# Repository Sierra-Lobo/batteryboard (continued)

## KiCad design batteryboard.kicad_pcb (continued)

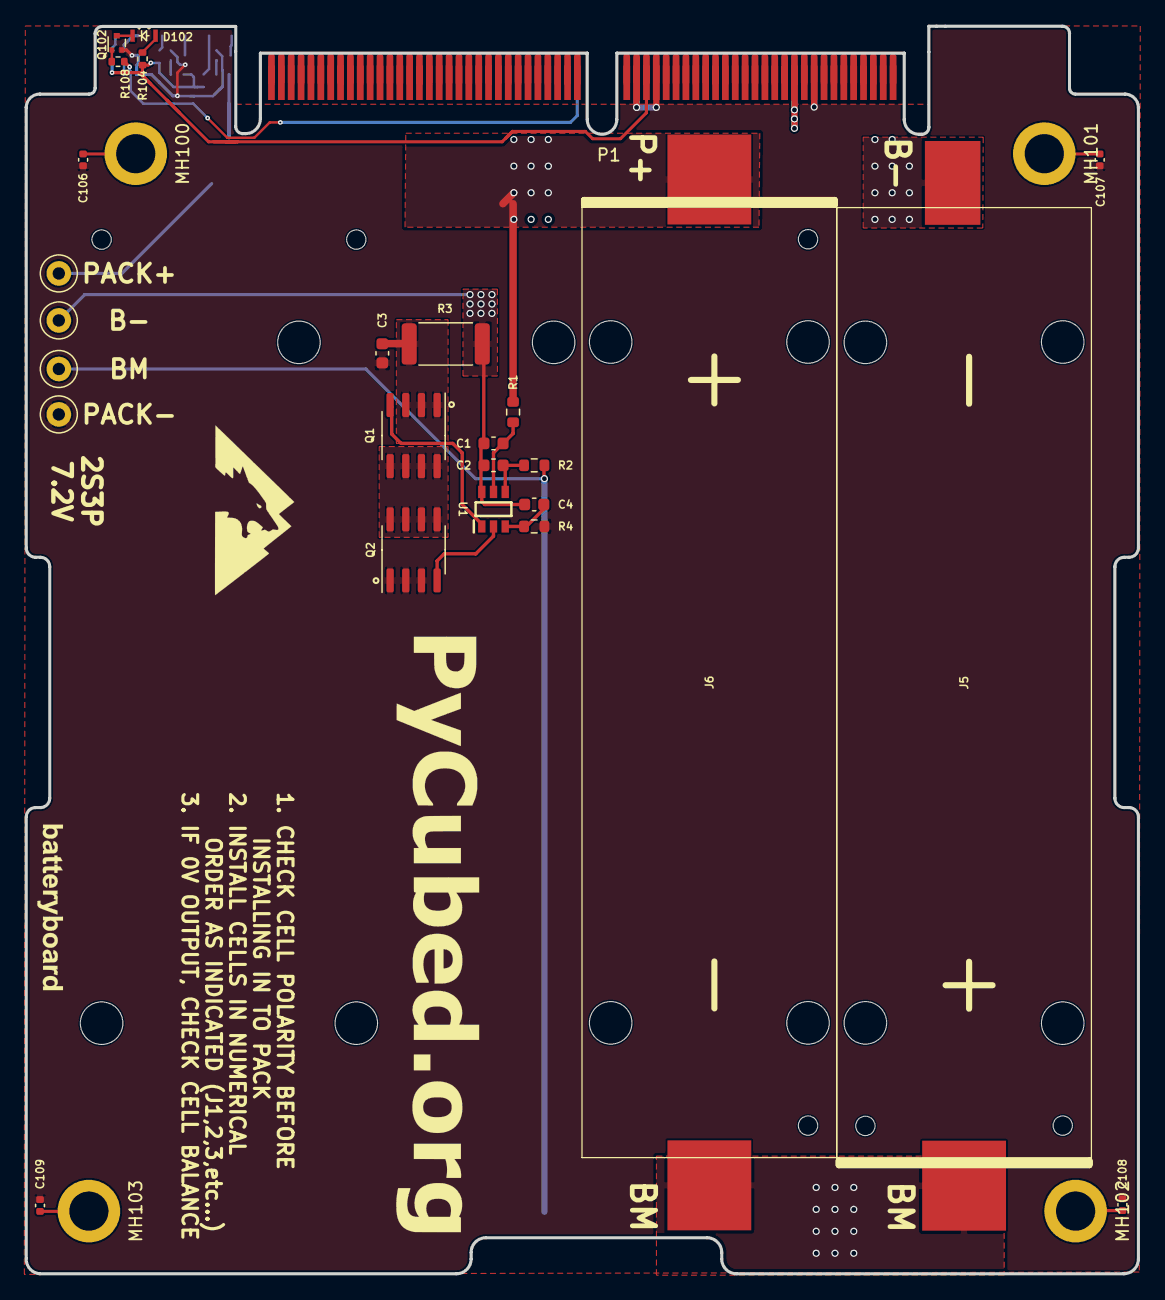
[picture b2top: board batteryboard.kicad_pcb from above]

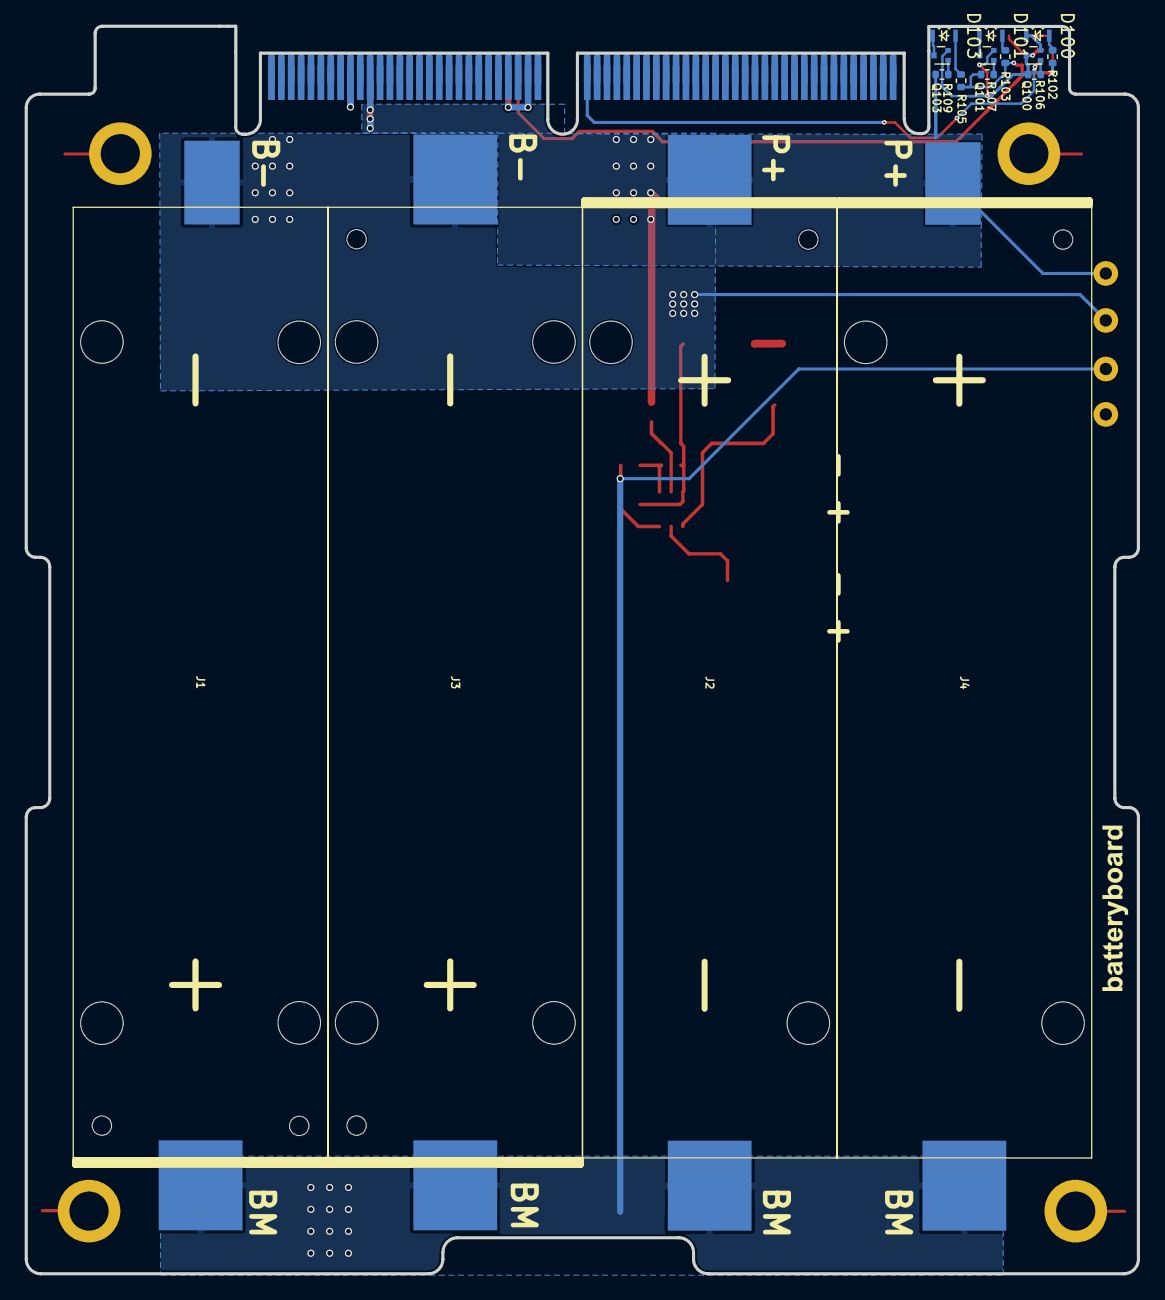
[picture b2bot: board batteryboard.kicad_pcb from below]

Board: 2 copper layers, 90.2 x 101.1 mm, 49 parts (17 on the bottom side), 26 nets.

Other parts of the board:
Ref**: Val**; battery_version
Ref**#2: Val**; battery_version
Ref**#3: Val**; pycubed_logo

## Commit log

2022-03-28 update folder, update gitignore
2022-03-28 renamed folder
2022-03-28 move license.txt
2022-04-11 rev B em
2022-04-12 Thermal relief and Pours
    changed thermal reliefs to solid. Changed a few pour clearances.
2022-04-12 final changes before fab
2022-04-12 updated gerbers
2022-04-12 zip'd fab files for easy ordering
2022-04-12 BOM updates for revB
2023-03-21 renamed folders
2023-03-24 update project to kicad 7 format
2023-06-20 revB1
